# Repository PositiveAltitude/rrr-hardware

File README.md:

# RRR
This repo contains design files for experimental "RRR" flight computer for Thrust Vector Control model rockets. The main idea is to use an ESP32-C3 microcontroller (RISC V) and Rust programming language. So the name is Risc Rust Rocket.
Please keep in mind that this is a prototype and a proof of concept, so expect issues and design mistakes. All parts were sourced from LCSC, so you can find LCSC part numbers populated for every component.

### Know issues
- Inertia measurement unit Pin 12 (CSB) is wrongly connected to GND. It should be connected to VCC or floating. It is possible to fix this by carefully cutting two traces with a sharp knife under a microscope.
- Pyro channels transistors placed incorrectly. That could be fixed if you solder them rotated 120 degrees counter-clockwise. Looks quite ugly but possible.

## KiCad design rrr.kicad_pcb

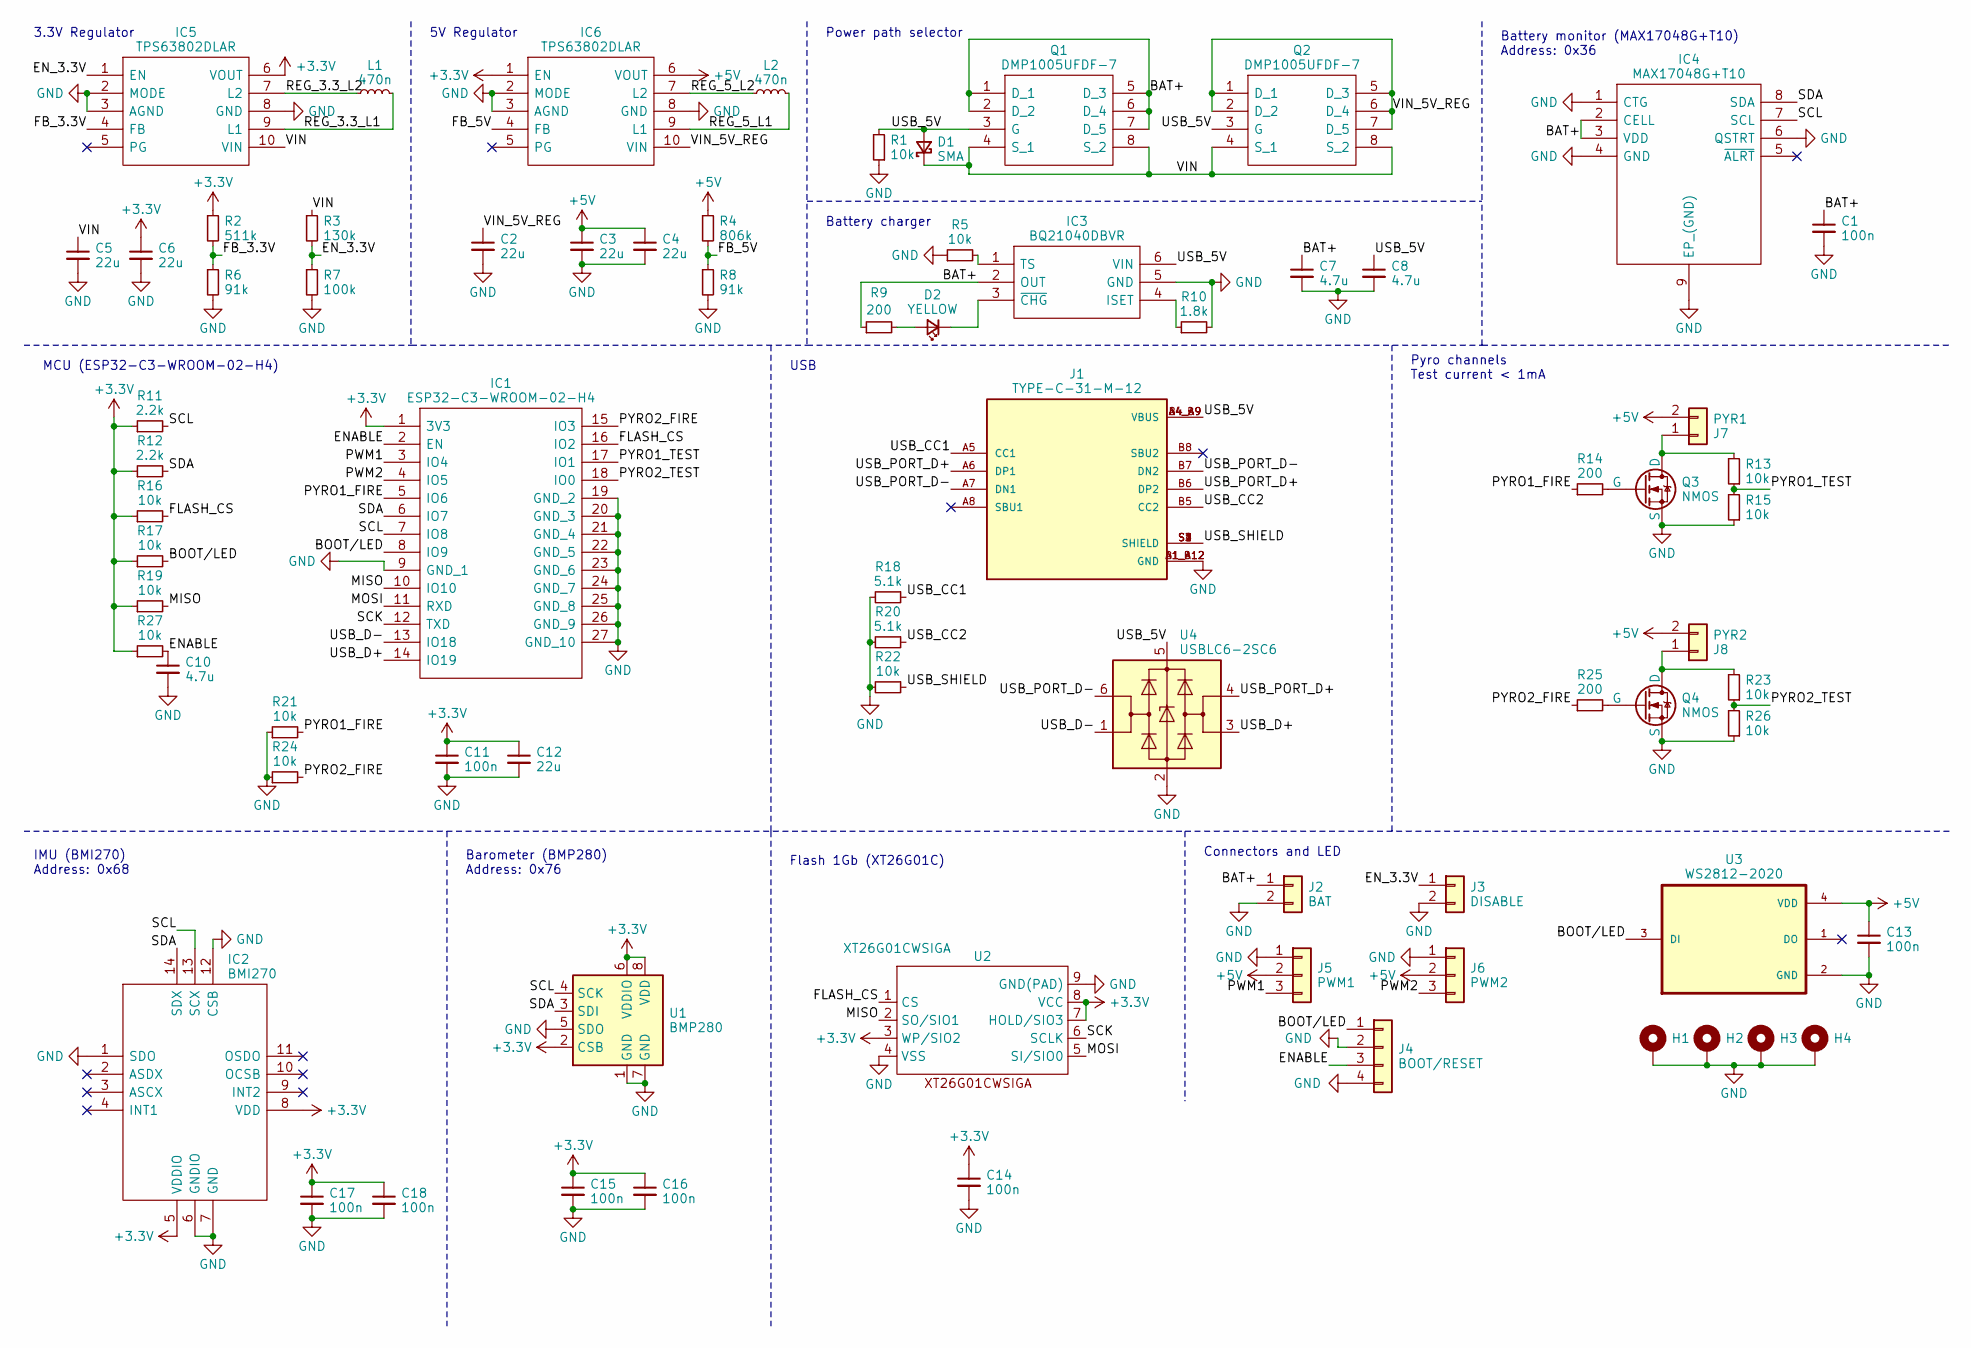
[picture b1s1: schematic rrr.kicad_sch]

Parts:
C1, C11, C13, C14, C15, C16, C17, C18: 100n; C_0402_1005Metric_Pad0.74x0.62mm_HandSolder; LCSC C85858
C2, C3, C4, C5, C6, C12: 22u; C_0805_2012Metric_Pad1.18x1.45mm_HandSolder; LCSC C86816
C7, C8, C10: 4.7u; C_0603_1608Metric_Pad1.08x0.95mm_HandSolder; LCSC C162274
D1: SMA; D_SMA_Handsoldering; LCSC C2983557
D2: YELLOW; LED_0603_1608Metric_Pad1.05x0.95mm_HandSolder; LCSC C72038
H1, H2, H3, H4: MountingHole_2.2mm_M2_Pad_Via
IC1: ESP32-C3-WROOM-02-H4; ESP32C3WROOM02H4; Mouser Part Number 356-ESP32C3WROOM02H4
IC2: BMI270; QFN50P300X250X87-14N; Mouser Part Number 262-BMI270
IC3: BQ21040DBVR; SOT95P280X145-6N; Mouser Part Number 595-BQ21040DBVR
IC4: MAX17048G+T10; SON50P200X200X80-9N-D; Mouser Part Number 700-MAX17048G+T10
IC5, IC6: TPS63802DLAR; Mouser Part Number 595-TPS63802DLAR
J1: TYPE-C-31-M-12; HRO_TYPE-C-31-M-12; PARTREV 2020.12.08; LCSC C165948
J2: BAT; JST_XH_B2B-XH-A_1x02_P2.50mm_Vertical; LCSC C158012
J3: DISABLE; PinHeader_2x01_P2.54mm_Horizontal; LCSC C492430
J4: BOOT/RESET; PinHeader_2x02_P2.54mm_Horizontal; LCSC C492430
J5: PWM1; JST_XH_B3B-XH-A_1x03_P2.50mm_Vertical; LCSC C144394
J6: PWM2; JST_XH_B3B-XH-A_1x03_P2.50mm_Vertical; LCSC C144394
J7: PYR1; JST_XH_B2B-XH-A_1x02_P2.50mm_Vertical; LCSC C158012
J8: PYR2; JST_XH_B2B-XH-A_1x02_P2.50mm_Vertical; LCSC C158012
L1, L2: 470n; L_1008_2520Metric_Pad1.43x2.20mm_HandSolder; LCSC C1333867
Q1, Q2: DMP1005UFDF-7; DMP1005UFDF7; Mouser Part Number 621-DMP1005UFDF-7
Q3, Q4: NMOS; SOT-23; LCSC C3280164
R1, R5, R13, R15, R16, R17, R19, R21, R22, R23, R24, R26, R27: 10k; R_0402_1005Metric_Pad0.72x0.64mm_HandSolder; LCSC C60490
R2: 511k; R_0402_1005Metric_Pad0.72x0.64mm_HandSolder; LCSC C163461
R3: 130k; R_0402_1005Metric_Pad0.72x0.64mm_HandSolder; LCSC C93946
R4: 806k; R_0402_1005Metric_Pad0.72x0.64mm_HandSolder; LCSC C3016043
R6, R8: 91k; R_0402_1005Metric_Pad0.72x0.64mm_HandSolder; LCSC C327323
R7: 100k; R_0402_1005Metric_Pad0.72x0.64mm_HandSolder; LCSC C60491
R9, R14, R25: 200; R_0402_1005Metric_Pad0.72x0.64mm_HandSolder; LCSC C114764
R10: 1.8k; R_0402_1005Metric_Pad0.72x0.64mm_HandSolder; LCSC C163481
R11, R12: 2.2k; R_0402_1005Metric_Pad0.72x0.64mm_HandSolder; LCSC C114762
R18, R20: 5.1k; R_0402_1005Metric_Pad0.72x0.64mm_HandSolder; LCSC C105872
U1: BMP280; Bosch_LGA-8_2x2.5mm_P0.65mm_ClockwisePinNumbering; LCSC C83291
U2: XT26G01CWSIGA; WSON-8-1EP_8x6mm_P1.27mm_EP3.4x4.3mm; LCSC C2833378
U3: WS2812-2020; LED_WS2812-2020; PARTREV V1.3; LCSC C965555
U4: USBLC6-2SC6; SOT-23-6; LCSC C7519

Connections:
+3.3V: C6.1, C11.1, C12.1, C14.1, C15.1, C16.1, C17.1, C18.1, IC1.1 (3V3), IC2.5 (VDDIO), IC2.8 (VDD), IC5.6 (VOUT), IC6.1 (EN), R2.1, R11.1, R12.1, R16.1, R17.1, R19.1, R27.1, U1.2 (CSB), U1.6 (VDDIO), U1.8 (VDD), U2.3 (WP/SIO2), U2.7 (HOLD/SIO3), U2.8 (VCC)
+5V: C3.1, C4.1, C13.1, IC6.6 (VOUT), J5.2, J6.2, J7.2, J8.2, R4.1, U3.4 (VDD)
/BAT+: C1.1, C7.1, IC3.2 (OUT), IC4.2 (CELL), IC4.3 (VDD), J2.1, Q1.1 (D_1), Q1.2 (D_2), Q1.5 (D_3), Q1.6 (D_4), Q1.7 (D_5), R9.1
/BOOT/LED: IC1.8 (IO9), J4.1, R17.2, U3.3 (DI)
/ENABLE: C10.1, IC1.2 (EN), J4.3, R27.2
/EN_3.3V: IC5.1 (EN), J3.1, R3.2, R7.1
/FB_3.3V: IC5.4 (FB), R2.2, R6.1
/FB_5V: IC6.4 (FB), R4.2, R8.1
/FLASH_CS: IC1.16 (IO2), R16.2, U2.1 (CS)
/MISO: IC1.10 (IO10), R19.2, U2.2 (SO/SIO1)
/MOSI: IC1.11 (RXD), U2.5 (SI/SIO0)
/PWM1: IC1.3 (IO4), J5.3
/PWM2: IC1.4 (IO5), J6.3
/PYRO1_FIRE: IC1.5 (IO6), R14.1, R21.2
/PYRO1_TEST: IC1.17 (IO1), R13.1, R15.2
/PYRO2_FIRE: IC1.15 (IO3), R24.2, R25.1
/PYRO2_TEST: IC1.18 (IO0), R23.1, R26.2
/REG_3.3_L1: IC5.9 (L1), L1.2
/REG_3.3_L2: IC5.7 (L2), L1.1
/REG_5_L1: IC6.9 (L1), L2.2
/REG_5_L2: IC6.7 (L2), L2.1
/SCK: IC1.12 (TXD), U2.6 (SCLK)
/SCL: IC1.7 (IO8), IC2.13 (SCX), IC4.7 (SCL), R11.2, U1.4 (SCK)
/SDA: IC1.6 (IO7), IC2.14 (SDX), IC4.8 (SDA), R12.2, U1.3 (SDI)
/USB_5V: C8.1, D1.2 (A), IC3.6 (VIN), J1.A4_B9 (VBUS), J1.B4_A9 (VBUS), Q1.3 (G), Q2.3 (G), R1.2, U4.5 (VBUS)
/USB_CC1: J1.A5 (CC1), R18.1
/USB_CC2: J1.B5 (CC2), R20.1
/USB_D+: IC1.14 (IO19), U4.3 (I/O2)
/USB_D-: IC1.13 (IO18), U4.1 (I/O1)
/USB_PORT_D+: J1.A6 (DP1), J1.B6 (DP2), U4.4 (I/O2)
/USB_PORT_D-: J1.A7 (DN1), J1.B7 (DN2), U4.6 (I/O1)
/USB_SHIELD: J1.S1 (SHIELD), J1.S2 (SHIELD), J1.S3 (SHIELD), J1.S4 (SHIELD), R22.1
/VIN: C5.1, D1.1 (K), IC5.10 (VIN), Q1.4 (S_1), Q1.8 (S_2), Q2.4 (S_1), Q2.8 (S_2), R3.1
/VIN_5V_REG: C2.1, IC6.10 (VIN), Q2.1 (D_1), Q2.2 (D_2), Q2.5 (D_3), Q2.6 (D_4), Q2.7 (D_5)
GND: C1.2, C2.2, C3.2, C4.2, C5.2, C6.2, C7.2, C8.2, C10.2, C11.2, C12.2, C13.2, C14.2, C15.2, C16.2, C17.2, C18.2, H1.1, H2.1, H3.1, H4.1, IC1.9 (GND_1), IC1.19 (GND_2), IC1.20 (GND_3), IC1.21 (GND_4), IC1.22 (GND_5), IC1.23 (GND_6), IC1.24 (GND_7), IC1.25 (GND_8), IC1.26 (GND_9), IC1.27 (GND_10), IC2.1 (SDO), IC2.6 (GNDIO), IC2.7 (GND), IC2.12 (CSB), IC3.5 (GND), IC4.1 (CTG), IC4.4 (GND), IC4.6 (QSTRT), IC4.9 (EP_(GND)), IC5.2 (MODE), IC5.3 (AGND), IC5.8 (GND), IC6.2 (MODE), IC6.3 (AGND), IC6.8 (GND), J1.A1_B12 (GND), J1.B1_A12 (GND), J2.2, J3.2, J4.2, J4.4, J5.1, J6.1, Q3.3 (S), Q4.3 (S), R1.1, R5.1, R6.2, R7.2, R8.2, R10.2, R15.1, R18.2, R20.2, R21.1, R22.2, R24.1, R26.1, U1.1 (GND), U1.5 (SDO), U1.7 (GND), U2.4 (VSS), U2.9 (GND(PAD)), U3.2 (GND), U4.2 (GND)
unnamed: D2.2 (A), R9.2
unnamed: D2.1 (K), IC3.3 (~CHG)
unnamed: IC3.4 (ISET), R10.1
unnamed: IC3.1 (TS), R5.2
unnamed: J7.1, Q3.1 (D), R13.2
unnamed: J8.1, Q4.1 (D), R23.2
unnamed: Q3.2 (G), R14.2
unnamed: Q4.2 (G), R25.2

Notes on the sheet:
Connectors and LED
IMU (BMI270) Address: 0x68
Flash 1Gb (XT26G01C)
3.3V Regulator
USB
Barometer (BMP280) Address: 0x76
5V Regulator
Pyro channels Test current < 1mA
Battery monitor (MAX17048G+T10) Address: 0x36
MCU (ESP32-C3-WROOM-02-H4)
Battery charger
Power path selector

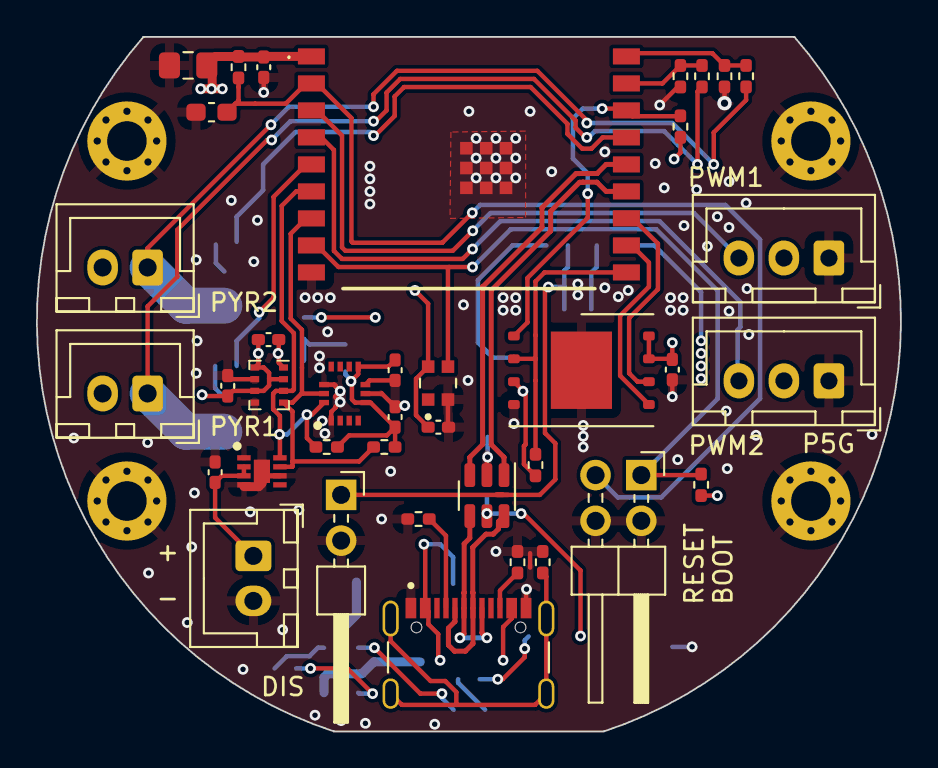
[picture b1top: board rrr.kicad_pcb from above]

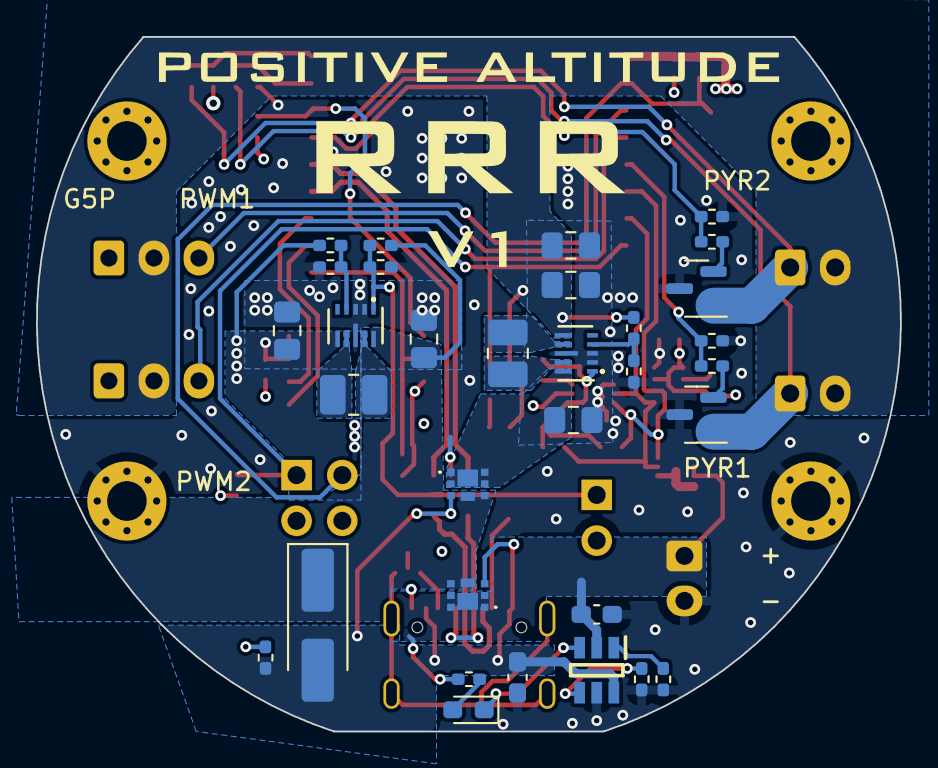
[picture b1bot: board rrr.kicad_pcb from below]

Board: 4 copper layers, 48.0 x 38.6 mm, 74 parts (32 on the bottom side), 43 nets.

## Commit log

2023-12-24 First version
2023-12-24 Added README
2023-12-24 README updated
2024-08-17 Update README.md (typos)
